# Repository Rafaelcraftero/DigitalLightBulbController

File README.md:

**Introducción**

Se desarrollará una placa de circuito impreso, más bien conocida como PCB. Para ellos usaremos la herramienta KiCad, la cual nos ayudara a la hora de diseñar el esquema que queremos seguir para realizarla y ver una fiel representación de como quedara nuestra placa una vez finalizada (layout), así como la generación de los archivos necesarios para su fabricación (Gerbers). Para realizar este bloque a parte de la PCB necesitaremos mas elementos, entre ellos están el
Arduino Pro Mini del bloque anterior, en concreto el 328P ya que es el que tiene mas memoria, el módulo de radiofrecuencia NRF24 y MySensors para comunicarnos remotamente a la horadel testeo.

Una vez que hayamos hecho todo el proceso de creación y diseño, le enviaremos los archivos necesarios al encargado de fabricarnos la placa.

**Diseño de la PCB**

*Especificación verbal del sistema:*

- Se pretende diseñar una placa para implementar nodos MYSENSOR para control de
encendido/apagado de luces mediante RELÉ

Para ello seguiremos los siguientes pasos:

- Diseño básico del sistema
- Listado de componentes del diseño electrónico
- Creación de la “board” (placa)
- Generación de los ficheros gerbers
- Sobre la Memoria del Diseño de la PCB

Diseño esquemático del circuito anterior

Diseño de la PCB

Generamos los Gerbers

Nota: Esta es una versión antigua, en la nueva están Corregidos los errores de hueyas

Soldamos los componentes a la PCB

**Test de la PCB**

Al hacer el test nos dimos cuenta que la parte digital funciona correctamente sin embargo la parte analógica tiene un error en el diseño y está conectada el 5V a tierra y tierra a 5V. Posteriormente se ha arreglado el diseño y subido a github.

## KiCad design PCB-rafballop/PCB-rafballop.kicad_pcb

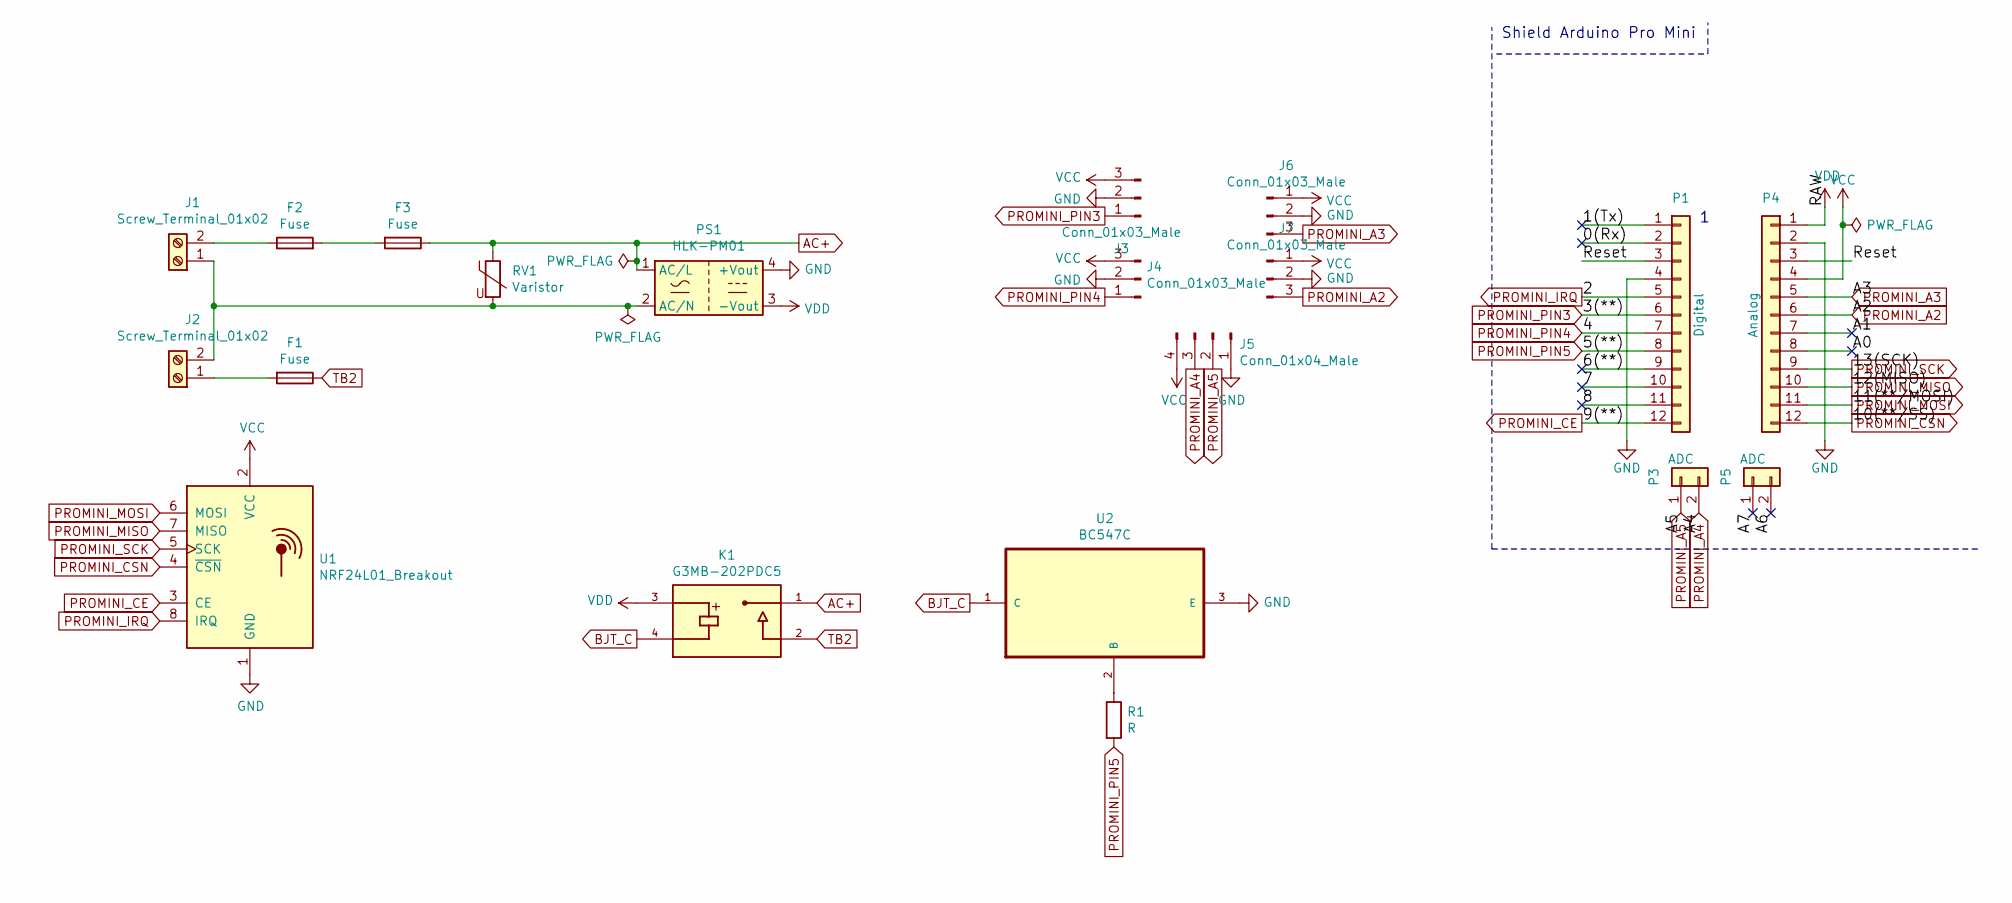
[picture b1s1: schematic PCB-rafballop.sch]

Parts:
F1, F2, F3: Fuse; R_Axial_DIN0414_L11.9mm_D4.5mm_P15.24mm_Horizontal
J1, J2: Screw_Terminal_01x02; TerminalBlock_Altech_AK300-2_P5.00mm
J3, J4, J6, J7: Conn_01x03_Male; PinHeader_1x03_P2.54mm_Vertical
J5: Conn_01x04_Male; PinHeader_1x04_P2.54mm_Vertical
K1: G3MB-202PDC5; RELAY_G3MB-202PDC5; PARTREV J091-E1-1A
P1: Digital; Socket_Strip_Arduino_1x12
P3, P5: ADC; Socket_Strip_Arduino_1x02
P4: Analog; Socket_Strip_Arduino_1x12
PS1: HLK-PM01; Converter_ACDC_HiLink_HLK-PMxx
R1: R; R_1206_3216Metric_Pad1.30x1.75mm_HandSolder
RV1: Varistor; RV_Disc_D12mm_W6.2mm_P7.5mm
U1: NRF24L01_Breakout; nRF24L01_Breakout
U2: BC547C; TO127P254X732-3; MPN BC547C

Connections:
/0(Rx): P1.2
/1(Tx): P1.1
/6(**): P1.9
/7: P1.10
/8: P1.11
/A0: P4.8
/A1: P4.7
/Reset: P1.3, P4.3
AC+: F3.1, K1.1, PS1.1 (AC/L), RV1.1
BJT_C: K1.4, U2.1 (C)
GND: J3.2, J4.2, J5.1, J6.2, J7.2, P1.4, P4.2, PS1.4 (+Vout), U1.1 (GND), U2.3 (E)
unnamed: F1.2, J2.1
unnamed: F2.1, J1.2
unnamed: F2.2, F3.2
unnamed: J1.1, J2.2, PS1.2 (AC/N), RV1.2
unnamed: R1.1, U2.2 (B)
PROMINI_A2: J7.3, P4.6
PROMINI_A3: J6.3, P4.5
PROMINI_A4: J5.3, P3.2
PROMINI_A5: J5.2, P3.1
PROMINI_CE: P1.12, U1.3 (CE)
PROMINI_CSN: P4.12, U1.4 (~CSN)
PROMINI_IRQ: P1.5, U1.8 (IRQ)
PROMINI_MISO: P4.10, U1.7 (MISO)
PROMINI_MOSI: P4.11, U1.6 (MOSI)
PROMINI_PIN3: J3.1, P1.6
PROMINI_PIN4: J4.1, P1.7
PROMINI_PIN5: P1.8, R1.2
PROMINI_SCK: P4.9, U1.5 (SCK)
TB2: F1.1, K1.2
VCC: J3.3, J4.3, J5.4, J6.1, J7.1, P4.4, U1.2 (VCC)
VDD: K1.3, P4.1, PS1.3 (-Vout)

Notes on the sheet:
Shield Arduino Pro Mini

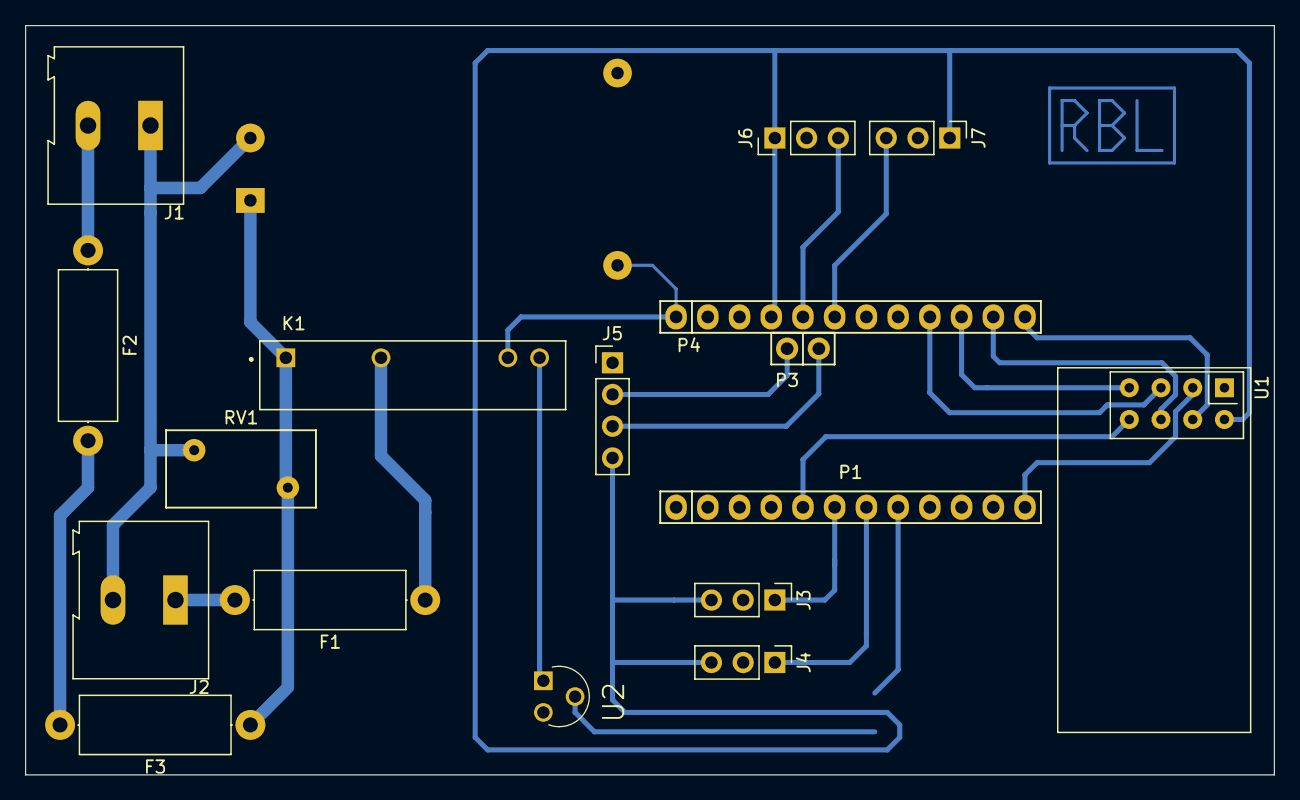
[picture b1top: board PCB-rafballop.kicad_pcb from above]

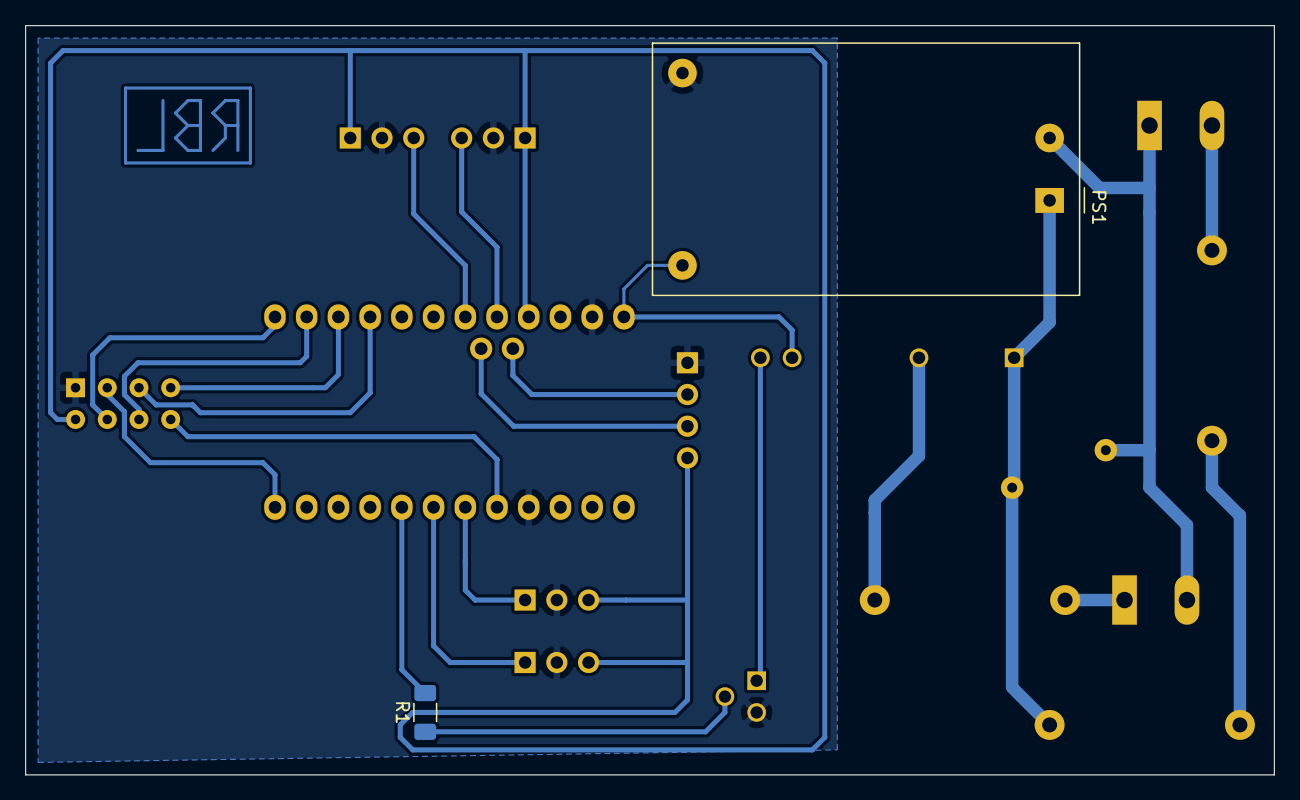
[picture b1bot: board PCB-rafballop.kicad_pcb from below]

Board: 2 copper layers, 100.0 x 60.0 mm, 19 parts (2 on the bottom side), 25 nets.
